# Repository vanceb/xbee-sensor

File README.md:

# xbee-sensor
Solar/battery powered sensor that uses XBee radios for communication

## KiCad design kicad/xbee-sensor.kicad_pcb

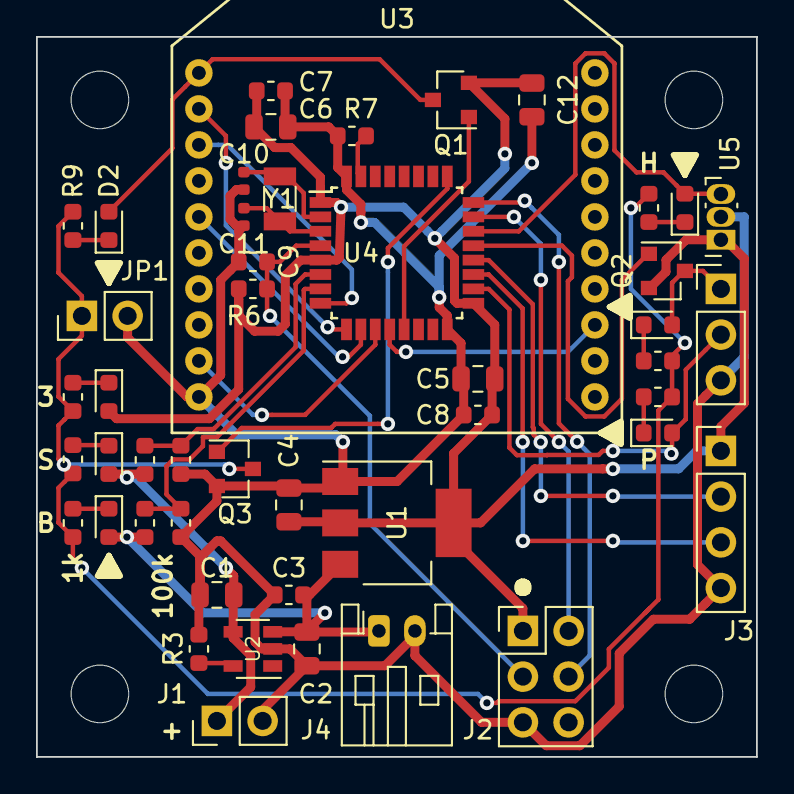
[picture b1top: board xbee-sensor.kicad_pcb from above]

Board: 2 copper layers, 40.0 x 40.0 mm, 48 parts (0 on the bottom side), 35 nets.

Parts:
C1, C2: 4.7uF; C_0805_2012Metric
C3, C7, C8, C9: 100nF; C_0603_1608Metric
C4, C12: 10uF; C_0805_2012Metric
C5, C6: 1uF; C_0805_2012Metric
C10, C11: 10pF; C_0402_1005Metric
D1, D2, D3, D4, D5, D6, D7: LED; LED_0603_1608Metric
J1: Solar; PinHeader_1x02_P2.54mm_Vertical
J2: SWD; PinHeader_2x03_P2.54mm_Vertical
J3: I2C; PinHeader_1x04_P2.54mm_Vertical
J4: Battery; JST_PH_S2B-PH-K_1x02_P2.00mm_Horizontal
J5: PIR; PinHeader_1x03_P2.54mm_Vertical
JP1: LED_EN; PinHeader_1x02_P2.54mm_Vertical
Q1, Q2: NX2301P; SOT-23
Q3: SI2333DDS; SOT-23
R1, R2, R4, R5: 100k; R_0603_1608Metric
R3: 2k; R_0603_1608Metric
R6, R7: 10k; R_0603_1608Metric
R8, R9, R10, R11, R12, R13, R14: 1k; R_0603_1608Metric
U1: LD1117S33TR_SOT223; SOT-223-3_TabPin2
U2: MCP73831-2-OT; SOT-23-5
U3: XBee_Module_TH; XBee
U4: STM32L031K6Tx; LQFP-32_7x7mm_P0.8mm
U5: A3213; Allegro_SIP-3
Y1: Crystal; Crystal_SMD_3215-2Pin_3.2x1.5mm

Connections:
+3V3: C4.1, C5.1, C6.1, C7.1, C8.1, C12.2, D7.2, J2.1, J3.1, Q1.2, Q2.2, R6.1, U1.2, U4.1, U4.5, U4.17, U5.1
BATTERY: C2.1, C3.1, D6.2, J4.1, R4.1, U1.3, U2.3
BATTERY_SENSE: R4.2, R5.1, U4.7
BOOT0: R7.1, U4.31
EN_PIR: Q2.1, U4.21
EN_XBEE: Q1.1, U4.13
GND: C1.2, C2.2, C3.2, C4.2, C5.2, C6.2, C7.2, C8.2, C9.1, C10.1, C11.2, C12.1, J1.2, J2.5, J3.4, J4.2, J5.3, JP1.2, Q3.2, R2.2, R3.2, R5.2, R7.2, U1.1, U2.2, U3.10, U4.16, U4.32, U5.2
HALL: D3.2, U4.22, U5.3
I2C_SCL: J3.3, U4.19
I2C_SDA: J3.2, U4.20
LED_GND: JP1.1, Q3.3, R8.2, R9.2, R10.2, R11.2, R12.2, R13.2, R14.2
NRST: C9.2, J2.3, R6.2, U4.4
unnamed: C10.2, U4.2, Y1.2
unnamed: C11.1, U4.3, Y1.1
unnamed: D1.1, R8.1
unnamed: D2.1, R9.1
unnamed: D3.1, R10.1
unnamed: D4.1, R11.1
unnamed: D5.1, R12.1
unnamed: D6.1, R13.1
unnamed: D7.1, R14.1
unnamed: R3.1, U2.5
PIR: D4.2, J5.2, U4.18
PIR_PWR: D1.2, J5.1, Q2.3
SOLAR: C1.1, D5.2, J1.1, R1.1, U2.4
SOLAR_SENSE: R1.2, R2.1, U4.6
SWCLK: J2.4, U4.24
SWDIO: J2.2, U4.23
XBEE_PWR: D2.2, Q1.3, U3.1
XB_ON: U3.13, U4.12
XB_RESET: U3.5, U4.10
XB_RX: U3.2, U4.9
XB_SLEEP_REQ: U3.9, U4.11
XB_TX: U3.3, U4.8
~LED_EN: Q3.1, U4.25

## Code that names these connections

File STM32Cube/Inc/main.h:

/* USER CODE BEGIN Header */
/**
  ******************************************************************************
  * @file           : main.h
  * @brief          : Header for main.c file.
  *                   This file contains the common defines of the application.
  ******************************************************************************
  ** This notice applies to any and all portions of this file
  * that are not between comment pairs USER CODE BEGIN and
  * USER CODE END. Other portions of this file, whether 
  * inserted by the user or by software development tools
  * are owned by their respective copyright owners.
  *
  * COPYRIGHT(c) 2019 STMicroelectronics
  *
  * Redistribution and use in source and binary forms, with or without modification,
  * are permitted provided that the following conditions are met:
  *   1. Redistributions of source code must retain the above copyright notice,
  *      this list of conditions and the following disclaimer.
  *   2. Redistributions in binary form must reproduce the above copyright notice,
  *      this list of conditions and the following disclaimer in the documentation
  *      and/or other materials provided with the distribution.
  *   3. Neither the name of STMicroelectronics nor the names of its contributors
  *      may be used to endorse or promote products derived from this software
  *      without specific prior written permission.
  *
  * THIS SOFTWARE IS PROVIDED BY THE COPYRIGHT HOLDERS AND CONTRIBUTORS "AS IS"
  * AND ANY EXPRESS OR IMPLIED WARRANTIES, INCLUDING, BUT NOT LIMITED TO, THE
  * IMPLIED WARRANTIES OF MERCHANTABILITY AND FITNESS FOR A PARTICULAR PURPOSE ARE
  * DISCLAIMED. IN NO EVENT SHALL THE COPYRIGHT HOLDER OR CONTRIBUTORS BE LIABLE
  * FOR ANY DIRECT, INDIRECT, INCIDENTAL, SPECIAL, EXEMPLARY, OR CONSEQUENTIAL
  * DAMAGES (INCLUDING, BUT NOT LIMITED TO, PROCUREMENT OF SUBSTITUTE GOODS OR
  * SERVICES; LOSS OF USE, DATA, OR PROFITS; OR BUSINESS INTERRUPTION) HOWEVER
  * CAUSED AND ON ANY THEORY OF LIABILITY, WHETHER IN CONTRACT, STRICT LIABILITY,
  * OR TORT (INCLUDING NEGLIGENCE OR OTHERWISE) ARISING IN ANY WAY OUT OF THE USE
  * OF THIS SOFTWARE, EVEN IF ADVISED OF THE POSSIBILITY OF SUCH DAMAGE.
  *
  ******************************************************************************
  */
/* USER CODE END Header */

/* Define to prevent recursive inclusion -------------------------------------*/
#ifndef __MAIN_H
#define __MAIN_H

#ifdef __cplusplus
extern "C" {
#endif

/* Includes ------------------------------------------------------------------*/
#include "stm32l0xx_hal.h"

/* Private includes ----------------------------------------------------------*/
/* USER CODE BEGIN Includes */

/* USER CODE END Includes */

/* Exported types ------------------------------------------------------------*/
/* USER CODE BEGIN ET */

/* USER CODE END ET */

/* Exported constants --------------------------------------------------------*/
/* USER CODE BEGIN EC */

/* USER CODE END EC */

/* Exported macro ------------------------------------------------------------*/
/* USER CODE BEGIN EM */

/* USER CODE END EM */

/* Exported functions prototypes ---------------------------------------------*/
void Error_Handler(void);

/* USER CODE BEGIN EFP */

/* USER CODE END EFP */

/* Private defines -----------------------------------------------------------*/
#define SOLAR_SENSE_Pin GPIO_PIN_0
#define SOLAR_SENSE_GPIO_Port GPIOA
#define BATTERY_SENSE_Pin GPIO_PIN_1
#define BATTERY_SENSE_GPIO_Port GPIOA
#define XB_TX_Pin GPIO_PIN_2
#define XB_TX_GPIO_Port GPIOA
#define XB_RX_Pin GPIO_PIN_3
#define XB_RX_GPIO_Port GPIOA
#define XB_RESET_Pin GPIO_PIN_4
#define XB_RESET_GPIO_Port GPIOA
#define XB_SLEEP_REQ_Pin GPIO_PIN_5
#define XB_SLEEP_REQ_GPIO_Port GPIOA
#define XB_ON_Pin GPIO_PIN_6
#define XB_ON_GPIO_Port GPIOA
#define XB_EN_Pin GPIO_PIN_7
#define XB_EN_GPIO_Port GPIOA
#define PIR_Pin GPIO_PIN_8
#define PIR_GPIO_Port GPIOA
#define EN_PIR_Pin GPIO_PIN_11
#define EN_PIR_GPIO_Port GPIOA
#define HALL_Pin GPIO_PIN_12
#define HALL_GPIO_Port GPIOA
#define LED_EN_Pin GPIO_PIN_15
#define LED_EN_GPIO_Port GPIOA
/* USER CODE BEGIN Private defines */

/* USER CODE END Private defines */

#ifdef __cplusplus
}
#endif

#endif /* __MAIN_H */

/************************ (C) COPYRIGHT STMicroelectronics *****END OF FILE****/

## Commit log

2019-02-12 Commit before V2 revisions
2019-02-13 Version 2.0 layout
2019-06-30 Created V2 ready for manufacture
2019-06-30 Code experimentation
2019-08-24 Version 2.0 boards
2019-08-24 Testing vscode and I2C display
2019-11-05 Corrected case sensitivity caused by move to linux from OSX
